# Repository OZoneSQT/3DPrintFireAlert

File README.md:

# 3DPrintFireAlert
DIY Fire Alert for 3D printers, with automatic power off

Clon and download. Then Import the ZIP-file, as a libery in Arduino IDE the guide is indside the exampel files

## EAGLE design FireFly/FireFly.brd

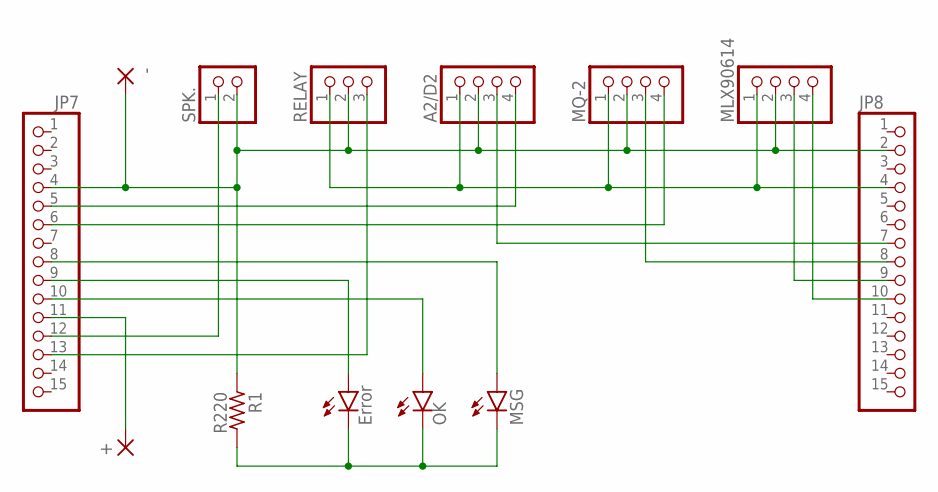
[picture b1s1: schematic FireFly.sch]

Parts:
+: WIREPADSMD1,27-254; SMD1,27-2,54
-: WIREPADSMD1,27-254; SMD1,27-2,54
A2/D2: PINHD-1X4; 1X04
JP7, JP8: PINHD-1X15; 1X15
LED2: OK; CHIPLED_0603
LED3: Error; CHIPLED_0603
MLX90614: PINHD-1X4; 1X04
MQ-2: PINHD-1X4; 1X04
MSG: LEDCHIPLED_0603; CHIPLED_0603
R1: R220; R0603
RELAY: PINHD-1X3; 1X03
SPK.: PINHD-1X2; 1X02

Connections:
unnamed: JP8.10, MLX90614.4
unnamed: JP8.9, MLX90614.3
unnamed: JP8.8, MQ-2.3
unnamed: JP7.6, MQ-2.4
unnamed: A2/D2.3, JP8.7
unnamed: -.1, A2/D2.2, JP7.4, JP8.2, MLX90614.2, MQ-2.2, R1.1, RELAY.2, SPK..2
unnamed: A2/D2.4, JP7.5
unnamed: JP7.13, RELAY.3
unnamed: JP7.12, SPK..1
unnamed: +.1, JP7.11
unnamed: JP7.10, LED2.A
unnamed: JP7.9, LED3.A
unnamed: JP7.8, MSG.A
unnamed: LED2.C, LED3.C, MSG.C, R1.2
unnamed: A2/D2.1, JP8.4, MLX90614.1, MQ-2.1, RELAY.1

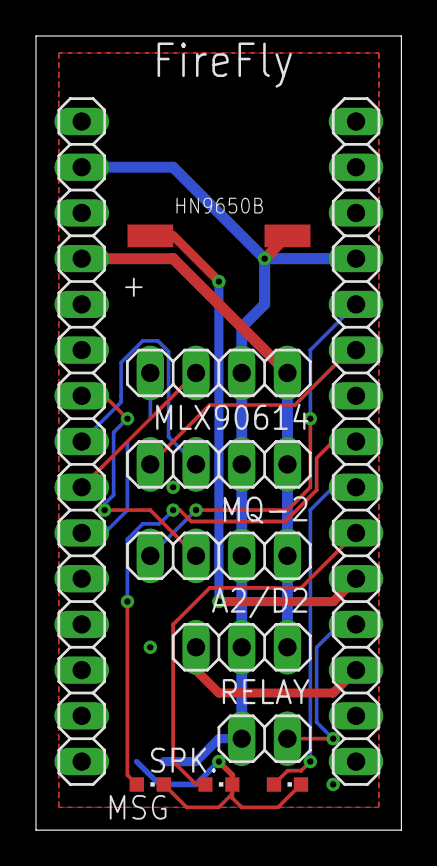
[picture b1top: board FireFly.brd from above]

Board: 2 copper layers, 20.3 x 44.1 mm, 13 parts (1 on the bottom side), 15 nets.

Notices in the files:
parts and their libraries:
rc-master-smd: Copyright (C) 2007, Bob Starr
